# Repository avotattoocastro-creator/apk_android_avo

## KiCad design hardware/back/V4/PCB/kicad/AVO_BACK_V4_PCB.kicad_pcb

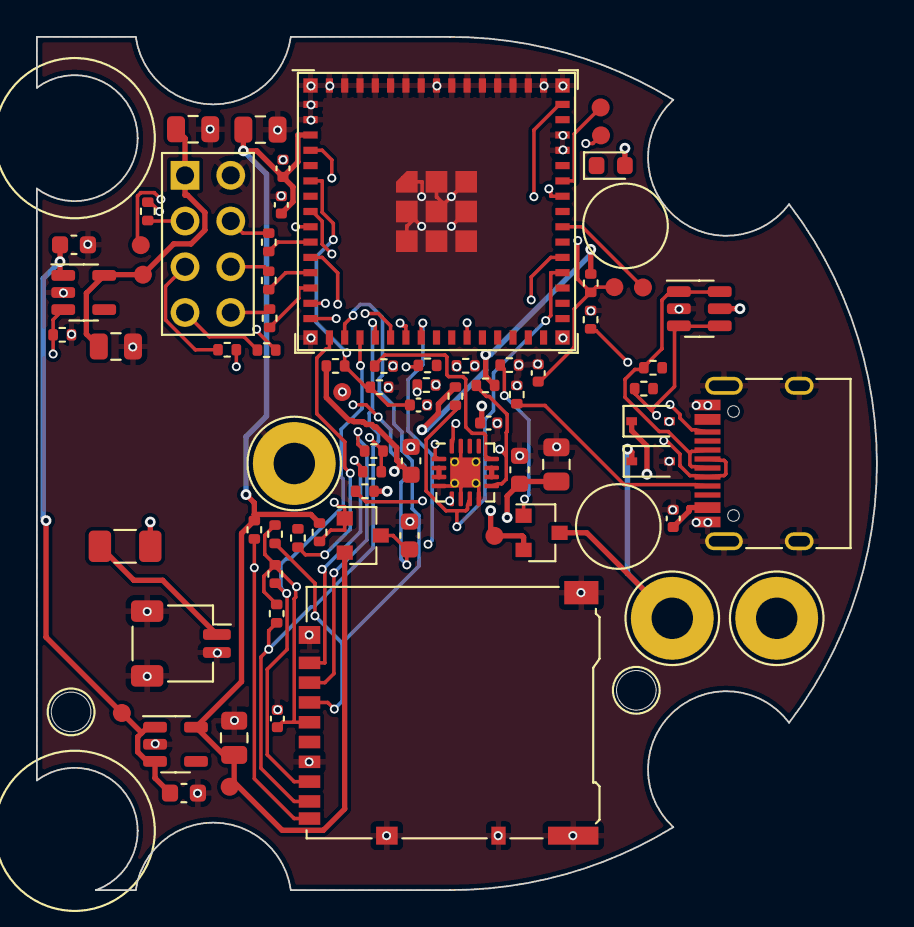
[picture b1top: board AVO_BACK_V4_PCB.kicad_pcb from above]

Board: 4 copper layers, 46.7 x 47.4 mm, 81 parts (0 on the bottom side), 53 nets.

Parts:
C18, C26, C27, C28: 1u; C_0402_1005Metric
C19, C20, C21, C40, C60: 10u 25V; C_0603_1608Metric
C22, C24, C61: 22u 10V; C_0805_2012Metric
C25, C34, C41: 100n; C_0402_1005Metric
C35, C62: 47u 6V3; C_0805_2012Metric
D1: LED rojo; LED_0603_1608Metric
D2, D3: TVS 5 V; D_SOD-323
F1: PTC 1,5 A; Fuse_1206_3216Metric
H1, H2: PIVOTE; AVO_Pivote_NPTH_D2.2
J1: USB-C 16P; USB_C_Receptacle_HRO_TYPE-C-31-M-12
J2: BATERÍA 1S; JST_SH_SM02B-SRSS-TB_1x02-1MP_P1.00mm_Horizontal
J3: microSD DM3AT; microSD_HC_Hirose_DM3AT-SF-PEJM5
J4: URTK1.2 (8 hilos); AVO_URTK_Pads_2x04_P2.54mm
MP1, MP2: PISADOR; AVO_Zona_Libre_R2.5
MR1, MR2: ANILLO; AVO_Zona_Libre_R4.6
P1: CONTACTO SYS; AVO_Contacto_M2_Tornillo
P2: CONTACTO BAT; AVO_Contacto_M2_Tornillo
P3: CONTACTO GND; AVO_Contacto_M2_Tornillo
Q3, Q4: AO3401A; SOT-23
R6, R7: 2k; R_0402_1005Metric
R8, R9, R10, R40, R47, R60: 100k; R_0402_1005Metric
R11, R30, R41, R42, R43, R44, R45: 10k; R_0402_1005Metric
R15, R50, R51, R52: 1k; R_0402_1005Metric
R16, R17: 5k1; R_0402_1005Metric
R18, R19, R46: 22R; R_0402_1005Metric
R32, R33: 1M; R_0402_1005Metric
R53, R54, R55: 330R; R_0402_1005Metric
RT2: NTC 10k B3380; R_0402_1005Metric
TP1: EN; TestPoint_Pad_D1.0mm
TP2: BOOT; TestPoint_Pad_D1.0mm
TP3: GND; TestPoint_Pad_D1.0mm
TP4: TXD0; TestPoint_Pad_D1.0mm
TP5: RXD0; TestPoint_Pad_D1.0mm
TP6: 3V3; TestPoint_Pad_D1.0mm
TP7: VBAT; TestPoint_Pad_D1.0mm
TP8: VSYS; TestPoint_Pad_D1.0mm
TP9: 3V3_ZED; TestPoint_Pad_D1.0mm
TP10: GPIO41; TestPoint_Pad_D1.0mm
U2: BQ24072RGTR; VQFN-16-1EP_3x3mm_P0.5mm_EP1.68x1.68mm_ThermalVias
U3: TLV75733PDBVR; SOT-23-5
U4: ESP32-S3-MINI-1U-N8; ESP32-S3-MINI-1U
U6: USBLC6-2SC6; SOT-23-6
U7: RT9080-33GJ5; SOT-23-5

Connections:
+3V3: C22.1, C24.1, C25.1, C26.1, D1.2, Q4.2, R9.2, R10.2, R11.2, R40.2, R47.2, TP6.1, U3.5, U4.3
+3V3_SD: C40.1, C41.1, J3.4, Q4.3, R41.2, R42.2, R43.2, R44.2, R45.2
+3V3_ZED: C61.1, C62.1, J4.1, TP9.1, U7.5
BAT_ADC: C34.1, R32.2, R33.1, U4.6
BAT_F: D3.1, F1.2, P2.1
BAT_G: Q3.1, R30.1
BAT_IN: F1.1, J2.1
BOOT: TP2.1, U4.4
CC1: J1.A5, R16.1
CC2: J1.B5, R17.1
CHG_EN2: R8.1, U2.5
CHG_ILIM: R7.1, U2.12
CHG_ISET: R6.1, U2.16
CHG_PG: R9.1, U2.7, U4.34
CHG_STAT: R10.1, U2.9, U4.35
CHG_TS: RT2.1, U2.1
EN: C27.1, R11.1, TP1.1, U4.45
GND: C18.2, C19.2, C20.2, C21.2, C22.2, C24.2, C25.2, C26.2, C27.2, C28.2, C34.2, C35.2, C40.2, C41.2, C60.2, C61.2, C62.2, D2.2, D3.2, J1.A1, J1.A12, J1.B1, J1.B12, J1.S1, J2.2, J2.MP, J3.6, J3.10, J3.11, J4.2, P3.1, R6.2, R7.2, R16.2, R17.2, R30.2, R33.2, R60.2, RT2.2, TP3.1, U2.4, U2.6, U2.8, U2.15, U2.17, U3.2, U4.1, U4.2, U4.42, U4.43, U4.46, U4.47, U4.48, U4.49, U4.50, U4.51, U4.52, U4.53, U4.54, U4.55, U4.56, U4.57, U4.58, U4.59, U4.60, U4.61, U4.62, U4.63, U4.64, U4.65, U6.2, U7.2
GPIO41: TP10.1, U4.37
LED: R15.1, U4.15
LED_K: D1.1, R15.2
S3_TX1: R50.1, U4.10
S3_TX2: R51.1, U4.12
S3_ZRST: R52.1, U4.13
SD_CD: J3.9, R47.1, U4.22
SD_CLK: J3.5, R46.2
SD_CLK0: R46.1, U4.16
SD_CMD: J3.3, R41.1, U4.17
SD_D0: J3.7, R42.1, U4.18
SD_D1: J3.8, R43.1, U4.19
SD_D2: J3.1, R44.1, U4.20
SD_D3: J3.2, R45.1, U4.21
SD_PWR_N: Q4.1, R40.1, U4.25
SYS_IN: D2.1, P1.1, Q3.3
U0RX: TP5.1, U4.40
U0TX: TP4.1, U4.39
USB_DM: R19.2, U4.23
USB_DM_C: J1.A7, J1.B7, R19.1, U6.3, U6.4
USB_DP: R18.2, U4.24
USB_DP_C: J1.A6, J1.B6, R18.1, U6.1, U6.6
VBAT: C20.1, Q3.2, R32.1, TP7.1, U2.2, U2.3
VBUS: C18.1, C28.1, J1.A4, J1.A9, J1.B4, J1.B9, U2.13, U6.5
VSYS: C19.1, C21.1, C35.1, C60.1, R8.2, TP8.1, U2.10, U2.11, U3.1, U3.3, U7.1
ZED_EN: R60.1, U4.14, U7.3
ZED_PPS: R55.2, U4.8
ZED_PPS_C: J4.7, R55.1
ZED_RST: J4.8, R52.2
ZED_RX1: J4.4, R50.2
ZED_RX2: J4.6, R51.2
ZED_TX1: R53.2, U4.9
ZED_TX1_C: J4.3, R53.1
ZED_TX2: R54.2, U4.11
ZED_TX2_C: J4.5, R54.1

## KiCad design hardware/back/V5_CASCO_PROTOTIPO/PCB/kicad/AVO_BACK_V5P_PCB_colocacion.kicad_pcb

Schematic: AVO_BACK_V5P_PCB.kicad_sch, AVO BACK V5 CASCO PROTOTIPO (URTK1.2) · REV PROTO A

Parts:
C18, C26, C27, C28, C36, C66, C67: 1u; C_0402_1005Metric; LCSC C52923
C19, C20, C21, C40, C60, C98: 10u 25V; C_0603_1608Metric; LCSC C96446
C22, C24, C35, C61, C99: 22u 10V; C_0805_2012Metric; LCSC C45783
C25, C34, C37, C38, C41, C42, C63, C68, C80, C90, C91, C92, C93, C94, C95, C96, C97: 100n; C_0402_1005Metric; LCSC C1525
C69: 22p; C_0402_1005Metric; LCSC C1555; not fitted
D2, D3: TVS 5 V; D_SOD-323; MPN PESD5V0S1BA; LCSC C2827694
D5, D6: BAT54C; SOT-23; MPN BAT54C; LCSC C2135
D10, D11, D12, D13, D14, D15, D16, D17: SK6812SIDE-A; AVO_SK6812SIDE-A_4.0x1.6mm; MPN SK6812SIDE-A (OPSCO); LCSC C5378721
D18: B5819W; D_SOD-123; MPN B5819W SL; LCSC C8598
F1, F2: PTC 1,5 A; Fuse_1206_3216Metric; MPN SMD1206P150TF; LCSC C20802
J2: BAT +; WirePad_D1.7_Drill0.9
J3: microSD DM3AT; microSD_HC_Hirose_DM3AT-SF-PEJM5; MPN DM3AT-SF-PEJM5; LCSC C114218
J6: BAT −; WirePad_D1.7_Drill0.9
J7: TÁCTIL; WirePad_D1.7_Drill0.9
J10: URTK1.2 9 pines; AVO_URTK1.2_Tira_1x09_P2.54
J11: URTK1.2 10 pines; AVO_URTK1.2_Tira_1x10_P2.54
J12, J13, J14, J15: GND PLACA ANTENA; WirePad_D2.0_Drill1.2
J16: USB-C programación; USB_C_Receptacle_HRO_TYPE-C-31-M-12; MPN TYPE-C-31-M-12 (HRO); LCSC C165948
L71: 1 µH; IND-SMD_L2.0-W1.6_FNR2016XXS; MPN WPN201610U1R0MT (Sunlord); LCSC C97016
P1: POGO VBUS; WirePad_D1.7_Drill0.9
P2: POGO D−; WirePad_D1.7_Drill0.9
P3: POGO D+; WirePad_D1.7_Drill0.9
P4: POGO GND; WirePad_D1.7_Drill0.9
P5: POGO AUX; WirePad_D1.7_Drill0.9
Q4, Q7: AO3401A; SOT-23; LCSC C15127
R6: 1k5; R_0402_1005Metric; LCSC C25867
R7: 2k; R_0402_1005Metric; LCSC C4109
R8, R9, R10, R13, R15, R21, R22, R26, R27, R40, R60: 100k; R_0402_1005Metric; LCSC C25741
R11, R17, R20, R41, R42, R43, R44, R45, R47: 10k; R_0402_1005Metric; LCSC C25744
R12: 68k; R_0402_1005Metric; LCSC C36871
R14, R32, R33: 1M; R_0402_1005Metric; LCSC C26083
R16, R50, R51, R52: 1k; R_0402_1005Metric; LCSC C11702
R18, R19, R46: 22R; R_0402_1005Metric; LCSC C25092
R23: 150k; R_0402_1005Metric; LCSC C25755
R24, R53, R54, R55: 330R; R_0402_1005Metric; LCSC C25104
R25: 620k; R_0402_1005Metric; LCSC C137952
R28, R29: 2k2; R_0402_1005Metric; LCSC C25879
R30, R31: 5k1; R_0402_1005Metric; LCSC C25905
RT2: NTC 10k B3380; R_0402_1005Metric; MPN NCP15XH103F03RC; LCSC C77131
TP1: EN; TestPoint_Pad_D1.0mm
TP2: BOOT; TestPoint_Pad_D1.0mm
TP3: GND; TestPoint_Pad_D1.0mm
TP4: TXD0; TestPoint_Pad_D1.0mm
TP5: RXD0; TestPoint_Pad_D1.0mm
TP6: 3V3; TestPoint_Pad_D1.0mm
TP7: VBAT; TestPoint_Pad_D1.0mm
TP8: VSYS; TestPoint_Pad_D1.0mm
TP9: 3V3_ZED; TestPoint_Pad_D1.0mm
TP10: 3V3_AON; TestPoint_Pad_D1.0mm
TP12: VLED; TestPoint_Pad_D1.0mm
TP13: SAFEBOOT; TestPoint_Pad_D1.0mm
U2: BQ24072RGTR; VQFN-16-1EP_3x3mm_P0.5mm_EP1.68x1.68mm_ThermalVias; MPN BQ24072RGTR; LCSC C140288
U3: TLV75733PDBVR; SOT-23-5; MPN TLV75733PDBVR; LCSC C485517
U4: ESP32-S3-WROOM-1U-N16R8; ESP32-S3-WROOM-1U; MPN ESP32-S3-WROOM-1U-N16R8; LCSC C3013946
U6: USBLC6-2SC6; SOT-23-6; LCSC C7519
U7: RT9080-33GJ5; SOT-23-5; MPN RT9080-33GJ5; LCSC C841192
U8: DRV5032FA; SOT-23; MPN DRV5032FADBZR; LCSC C140921
U9: XC6206P332MR; SOT-23; MPN XC6206P332MR-G (Torex); LCSC C5446
U10: TTP223-BA6-TD; SOT-23-6; MPN TTP223-BA6-TD (TDSEMIC); LCSC C42422127
U11: TPS61023DRLR; SOT-563_L1.6-W1.2-P0.50-LS1.6-BR; MPN TPS61023DRLR (TI); LCSC C919459
U12: MAX17048G+T10; TDFN-8_L2.0-W2.0-P0.50-BL-EP1.2; MPN MAX17048G+T10 (Analog Devices); LCSC C2682616
U13: LSM6DSV16X; ST_LGA-14L_2.5x3mm_P0.5mm; MPN LSM6DSV16XTR (ST); LCSC C5267406

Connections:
+3V3: C22.1, C24.1, C25.1, C26.1, C37.1, C38.1, C42.2, C80.1, Q4.2 (S), R9.2, R10.2, R11.2, R28.2, R29.2, R40.2, TP6.1, U3.5 (OUT), U4.2 (3V3), U8.1 (VCC), U13.5 (VDDIO), U13.8 (VDD), U13.12 (CS)
+3V3_AON: C67.1, C68.1, TP10.1, U9.2 (VOUT), U10.5 (VDD)
+3V3_SD: C40.1, C41.1, J3.4 (VDD), Q4.3 (D), R41.2, R42.2, R43.2, R44.2, R45.2
+3V3_ZED: C61.1, C63.1, J10.3 (3V3), J11.2 (3V3), TP9.1, U7.5 (VOUT)
BAT_ADC: C34.1, R32.2, R33.1, U4.38 (IO2 BAT_ADC)
BAT_F: F1.2, Q7.3 (D)
BAT_G: Q7.1 (G), R13.1
BAT_IN: F1.1, J2.1
BOOT: TP2.1, U4.27 (IO0 BOOT)
CHG_EN2: R8.1, U2.5 (EN2)
CHG_ILIM: R7.1, U2.12 (ILIM)
CHG_ISET: R6.1, U2.16 (ISET)
CHG_PG: R9.1, U2.7 (PGOOD), U4.31 (IO38 CHG_PG)
CHG_STAT: R10.1, U2.9 (CHG), U4.32 (IO39 CHG_STAT)
CHG_TMR: R12.1, U2.14 (TMR)
CHG_TS: RT2.1, U2.1 (TS)
EN: C27.1, R11.1, TP1.1, U4.3 (EN EN)
EN_3V3: C28.1, D5.3 (K), D6.3 (K), R14.1, U3.3 (EN)
GND: C18.2, C19.2, C20.2, C21.2, C22.2, C24.2, C25.2, C26.2, C27.2, C28.2, C34.2, C35.2, C36.2, C37.2, C38.2, C40.2, C41.2, C60.2, C61.2, C63.2, C66.2, C67.2, C68.2, C69.2, C80.2, C90.2, C91.2, C92.2, C93.2, C94.2, C95.2, C96.2, C97.2, C98.2, C99.2, D2.2 (A), D3.2 (A), D10.4 (GND), D11.4 (GND), D12.4 (GND), D13.4 (GND), D14.4 (GND), D15.4 (GND), D16.4 (GND), D17.4 (GND), J3.6 (VSS), J3.10 (DET_COM), J3.11 (SHELL), J6.1, J10.1 (GND), J11.1 (GND), J12.1, J13.1, J14.1, J15.1, J16.A1 (GND), J16.A12 (GND), J16.B1 (GND), J16.B12 (GND), J16.S1 (SHIELD), P4.1, R6.2, R7.2, R12.2, R13.2, R14.2, R15.2, R21.2, R23.2, R26.2, R27.2, R30.2, R31.2, R33.2, R60.2, RT2.2, TP3.1, U2.4 (CE), U2.6 (EN1), U2.8 (VSS), U2.15 (TD), U2.17 (EP), U3.2 (GND), U4.1 (GND), U4.40 (GND), U4.41 (GND), U6.2 (GND), U7.2 (GND), U8.3 (GND), U9.1 (VSS), U10.2 (VSS), U10.4 (AHLB), U10.6 (TOG), U11.4 (GND), U12.1 (CTG), U12.4 (GND), U12.6 (QSTRT), U12.9 (EP), U13.1 (SDO/SA0), U13.2 (SDx), U13.3 (SCx), U13.6 (GND), U13.7 (GND)
HALL: U4.39 (IO1 HALL), U8.2 (OUT)
I2C_SCL: R28.1, U4.34 (IO41 I2C_SCL), U12.7 (SCL), U13.13 (SCL)
I2C_SDA: R29.1, U4.35 (IO42 I2C_SDA), U12.8 (SDA), U13.14 (SDA)
IMU_INT1: U4.4 (IO4 IMU_INT1), U13.4 (INT1)
LED_D1: D10.1 (DIN), R24.2
LED_D2: D10.3 (DOUT), D11.1 (DIN)
LED_D3: D11.3 (DOUT), D12.1 (DIN)
LED_D4: D12.3 (DOUT), D13.1 (DIN)
LED_D5: D13.3 (DOUT), D14.1 (DIN)
LED_D6: D14.3 (DOUT), D15.1 (DIN)
LED_D7: D15.3 (DOUT), D16.1 (DIN)
LED_D8: D16.3 (DOUT), D17.1 (DIN)
LED_DIN_S3: R24.1, U4.24 (IO47 LED_DIN_S3)
LED_PWR: R27.1, U4.25 (IO48 LED_PWR), U11.2 (EN)
POGO_AUX: R20.2, R21.1, U4.33 (IO40 POGO_AUX)
POGO_AUX_C: D3.1 (K), P5.1, R20.1
POGO_VBUS: D2.1 (K), D18.1 (K), F2.1, P1.1
PWR_HOLD: D5.2 (A2), R15.1, U4.16 (IO46 PWR_HOLD)
S3_TX1: R50.1, U4.6 (IO6 S3_TX1)
S3_TX2: R51.1, U4.12 (IO8 S3_TX2)
S3_ZRST: R52.1, U4.17 (IO9 S3_ZRST)
SD_CLK: J3.5 (CLK), R46.2
SD_CLK0: R46.1, U4.20 (IO12 SD_CLK0)
SD_CMD: J3.3 (CMD), R41.1, U4.21 (IO13 SD_CMD)
SD_D0: J3.7 (DAT0), R42.1, U4.22 (IO14 SD_D0)
SD_D1: J3.8 (DAT1), R43.1, U4.8 (IO15 SD_D1)
SD_D2: J3.1 (DAT2), R44.1, U4.9 (IO16 SD_D2)
SD_D3: J3.2 (CD/DAT3), R45.1, U4.10 (IO17 SD_D3)
SD_G: C42.1, Q4.1 (G), R40.1, R47.2
SD_PWR_N: R47.1, U4.23 (IO21 SD_PWR_N)
TOUCH_E: J7.1, R16.1
TOUCH_I: C69.1, R16.2, U10.3 (I)
TOUCH_OUT: D5.1 (A1), R17.1, U10.1 (Q)
TOUCH_SENSE: R17.2, U4.19 (IO11 TOUCH_SENSE)
U0RX: TP5.1, U4.36 (RXD0 U0RX)
U0TX: TP4.1, U4.37 (TXD0 U0TX)
USBC_CC1: J16.A5 (CC1), R30.1
USBC_CC2: J16.B5 (CC2), R31.1
USBC_VBUS: D18.2 (A), J16.A4 (VBUS), J16.A9 (VBUS), J16.B4 (VBUS), J16.B9 (VBUS)
USB_DM: R19.2, U4.13 (IO19 D- USB_DM)
USB_DM_C: J16.A7 (D-), J16.B7 (D-), P2.1, R19.1, U6.3 (IO2), U6.4 (IO2)
USB_DP: R18.2, U4.14 (IO20 D+ USB_DP)
USB_DP_C: J16.A6 (D+), J16.B6 (D+), P3.1, R18.1, U6.1 (IO1), U6.6 (IO1)
VBAT: C20.1, C36.1, C66.1, Q7.2 (S), R32.1, TP7.1, U2.2 (BAT), U2.3 (BAT), U9.3 (VIN), U12.2 (CELL), U12.3 (VDD)
VBUS: C18.1, F2.2, R22.1, U2.13 (IN), U6.5 (VBUS)
VBUS_DET: D6.1 (A1), R22.2, R23.1, U4.11 (IO18 VBUS_DET)
VLED: C90.1, C91.1, C92.1, C93.1, C94.1, C95.1, C96.1, C97.1, C99.1, D10.2 (VDD), D11.2 (VDD), D12.2 (VDD), D13.2 (VDD), D14.2 (VDD), D15.2 (VDD), D16.2 (VDD), D17.2 (VDD), R25.1, TP12.1, U11.6 (VOUT)
VLED_FB: R25.2, R26.1, U11.1 (FB)
VLED_SW: L71.2, U11.5 (SW)
VSYS: C19.1, C21.1, C35.1, C60.1, C98.1, L71.1, R8.2, TP8.1, U2.10 (OUT), U2.11 (OUT), U3.1 (IN), U7.1 (VIN), U11.3 (VIN)
ZED_EN: R60.1, U4.18 (IO10 ZED_EN), U7.3 (EN)
ZED_PPS: R55.2, U4.7 (IO7 ZED_PPS)
ZED_PPS_C: J11.7 (PPS), R55.1
ZED_RST: J11.8 (RST), R52.2
ZED_RX1: J10.7 (RX/MOSI), R50.2
ZED_RX2: J10.5 (RX2), R51.2
ZED_SAFEBOOT: J11.9 (SAFE), TP13.1
ZED_TX1: R53.2, U4.5 (IO5 ZED_TX1)
ZED_TX1_C: J10.8 (TX/MISO), R53.1
ZED_TX2: R54.2, U4.15 (IO3 ZED_TX2)
ZED_TX2_C: J10.4 (TX2), R54.1

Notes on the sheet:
POGO MAGNÉTICO DE 5 CONTACTOS (por hilos): VBUS · D− · D+ · GND · AUX — carga y USB con el PC · ESD
ENCENDIDO Y APAGADO TOTAL: OR de diodos al EN del 3,3 V (táctil · POWER_HOLD GPIO46 · VBUS)
ANILLO DE LUZ: 7 × SK6812SIDE-A (GPIO47) a 4,3 V con elevador TPS61023 (EN = GPIO48, salida desconectada con EN = 0)
microSD (SDMMC 4 bits) · alimentación conmutada
GNSS EN MÓDULO URTK1.2 (ZED-F9P) POR TIRAS DE PINES: 3,3 V propio con EN (RT9080) · UART1 · UART2 · PPS · RESET
BATERÍA (hilos soldados) · PTC · medida por ADC
CARGADOR CON CAMINO DE POTENCIA (BQ24072) · batería 1S ≥ 2000 mAh
3,3 V PRINCIPAL (TLV75733P, 1 A) · EN = OR(táctil, POWER_HOLD, VBUS)
ESP32-S3-WROOM-1U-N16R8 (16 MB + PSRAM 8 MB) · BLE móvil + ESP-NOW cinchas · arranque
SENSOR HALL DRV5032 · encendido al poner la cápsula en la base del casco
3,3 V SIEMPRE ENCENDIDO (XC6206, ≈ 1 µA): táctil (la URTK1.2 lleva su pila de respaldo)
TÁCTIL SELLADO (TTP223, activo alto, directo) · electrodo por hilo · lectura en GPIO11
MEDIDOR DE BATERÍA MAX17048 (0x36, ModelGauge, ≈ 3 µA)
IMU LSM6DSV16X (0x6A) · INT1 → GPIO4 (despierta por movimiento)
BUS I²C (GPIO41 SCL · GPIO42 SDA, 400 kHz)
PUNTOS DE PRUEBA
Generado por fuente/avo_back_v5_pcb.py (mismo origen de datos que la placa). Las conexiones son etiquetas globales: dos pines con la misma etiqueta están unidos.

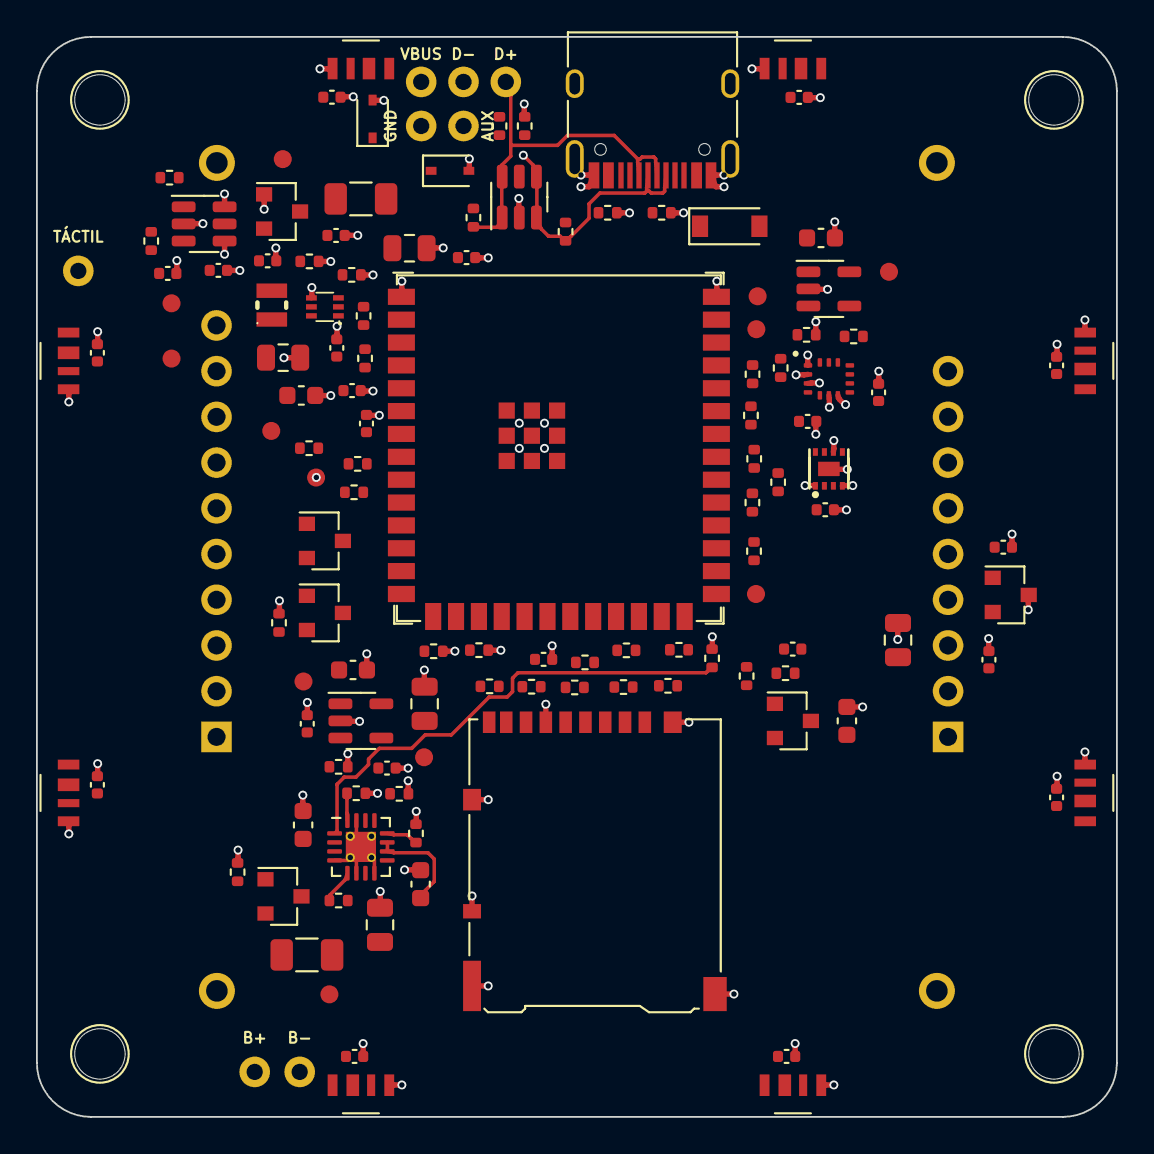
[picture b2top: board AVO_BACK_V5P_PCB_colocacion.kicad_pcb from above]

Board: 4 copper layers, 60.0 x 60.0 mm, 141 parts (0 on the bottom side), 80 nets.

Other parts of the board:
H1, H2, H3, H4: TALADRO M2,5; AVO_Taladro_NPTH_D2.8

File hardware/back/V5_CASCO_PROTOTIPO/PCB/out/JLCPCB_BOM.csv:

Comment,Designator,Footprint,LCSC Part #
"PTC 1,5 A","F1,F2",Fuse_1206_3216Metric,C20802
TVS 5 V,"D2,D3",D_SOD-323,C2827694
10k,"R11,R17,R20,R41,R42,R43,R44,R45,R47",R_0402_1005Metric,C25744
100k,"R8,R9,R10,R13,R15,R21,R27,R40,R60",R_0402_1005Metric,C25741
USBLC6-2SC6,U6,SOT-23-6,C7519
USB-C programación,J16,USB_C_Receptacle_HRO_TYPE-C-31-M-12,C165948
B5819W,D18,D_SOD-123,C8598
5k1,"R30,R31",R_0402_1005Metric,C25905
22R,"R18,R19,R46",R_0402_1005Metric,C25092
1k,"R16,R22,R50,R51,R52",R_0402_1005Metric,C11702
1k5,"R6,R23",R_0402_1005Metric,C25867
BQ24072RGTR,U2,VQFN-16-1EP_3x3mm_P0.5mm_EP1.68x1.68mm_ThermalVias,C140288
1u,"C18,C26,C27,C28,C36,C66,C67",C_0402_1005Metric,C52923
10u 25V,"C19,C20,C21,C40,C60,C98",C_0603_1608Metric,C96446
22u 10V,"C22,C24,C35,C61,C99",C_0805_2012Metric,C45783
2k,"R7,R25",R_0402_1005Metric,C4109
NTC 10k B3380,RT2,R_0402_1005Metric,C77131
68k,R12,R_0402_1005Metric,C36871
AO3401A,"Q4,Q7",SOT-23,C15127
1M,"R14,R32,R33",R_0402_1005Metric,C26083
100n,"C25,C34,C37,C38,C41,C42,C63,C68,C80,C90,C91,C92,C93,C94,C95,C96,C97",C_0402_1005Metric,C1525
TLV75733PDBVR,U3,SOT-23-5,C485517
BAT54C,"D5,D6",SOT-23,C2135
XC6206P332MR,U9,SOT-23,C5446
TTP223-BA6-TD,U10,SOT-23-6,C42422127
RT9080-33GJ5,U7,SOT-23-5,C841192
330R,"R24,R26,R53,R54,R55",R_0402_1005Metric,C25104
ESP32-S3-WROOM-1U-N16R8,U4,ESP32-S3-WROOM-1U,C3013946
SK6812SIDE-A,"D10,D11,D12,D13,D14,D15,D16,D17",AVO_SK6812SIDE-A_4.0x1.6mm,C5378721
TPS61023DRLR,U11,easyeda2kicad:SOT-563_L1.6-W1.2-P0.50-LS1.6-BR,C919459
1 µH,L71,easyeda2kicad:IND-SMD_L2.0-W1.6_FNR2016XXS,C97016
DRV5032FA,U8,SOT-23,C140921
microSD DM3AT,J3,microSD_HC_Hirose_DM3AT-SF-PEJM5,C114218
2k2,"R28,R29",R_0402_1005Metric,C25879
MAX17048G+T10,U12,easyeda2kicad:TDFN-8_L2.0-W2.0-P0.50-BL-EP1.2,C2682616
LSM6DSV16X,U13,ST_LGA-14L_2.5x3mm_P0.5mm,C5267406

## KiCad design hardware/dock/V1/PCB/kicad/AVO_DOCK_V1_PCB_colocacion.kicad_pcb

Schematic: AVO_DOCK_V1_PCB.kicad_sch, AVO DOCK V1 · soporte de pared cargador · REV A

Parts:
C1, C5: 47u 6V3; C_0805_2012Metric; LCSC C16780
C2, C8, C10, C13, C14, C16, C20, C21, C22, C23, C24, C25, C27, C28, C29, C40, C41, C42, C43, C44, C45, C46, C47: 100n; C_0402_1005Metric; LCSC C1525
C3, C15, C48, C49, C50, C51: 10u 25V; C_0603_1608Metric; LCSC C96446
C4: 100u 10V; CP_EIA-3528-21_Kemet-B; MPN TAJB107K010RNJ (AVX) o equivalente
C6, C7, C9: 22u 10V; C_0805_2012Metric; LCSC C45783
C11, C12: 1u; C_0402_1005Metric; LCSC C52923
C26: 4u7; C_0603_1608Metric; LCSC C19666
C30, C31: 18p; C_0402_1005Metric; LCSC C1549
D1, D10, D11, D12, D13, D14, D15, D16, D17: TVS 5 V; D_SOD-323; MPN PESD5V0S1BA; LCSC C2827694
F1: T1A 250V; Fuse_Littelfuse_372_D8.50mm; MPN Littelfuse 37211000411 (TR5, T 1 A)
F2: PTC 1,5 A; Fuse_1206_3216Metric; MPN SMD1206P150TF; LCSC C20802
J1: RED L; WirePad_D2.6_Drill1.3
J2: RED N; WirePad_D2.6_Drill1.3
J3: USB-C PC; USB_C_Receptacle_HRO_TYPE-C-31-M-12; MPN TYPE-C-31-M-12 (HRO); LCSC C165948
J4: PANTALLA 2" ST7789; JST_GH_SM08B-GHS-TB_1x08-1MP_P1.25mm_Horizontal; MPN SM08B-GHS-TB (JST)
P1: A VBUS; WirePad_D1.7_Drill0.9
P2: A D-; WirePad_D1.7_Drill0.9
P3: A D+; WirePad_D1.7_Drill0.9
P4: A GND; WirePad_D1.7_Drill0.9
P5: A AUX; WirePad_D1.7_Drill0.9
P6: B VBUS; WirePad_D1.7_Drill0.9
P7: B D-; WirePad_D1.7_Drill0.9
P8: B D+; WirePad_D1.7_Drill0.9
P9: B GND; WirePad_D1.7_Drill0.9
P10: B AUX; WirePad_D1.7_Drill0.9
P11: GA +5V; WirePad_D1.7_Drill0.9
P12: GA GND; WirePad_D1.7_Drill0.9
P13: GA MTCK; WirePad_D1.7_Drill0.9
P14: GB +5V; WirePad_D1.7_Drill0.9
P15: GB GND; WirePad_D1.7_Drill0.9
P16: GB MTCK; WirePad_D1.7_Drill0.9
P20: PULSADOR; WirePad_D1.7_Drill0.9
P21: PULSADOR GND; WirePad_D1.7_Drill0.9
PS1: IRM-20-5; Converter_ACDC_MeanWell_IRM-20-xx_THT; MPN Mean Well IRM-20-5 (5 V 4 A)
Q1, Q1B, Q2: AO3401A; SOT-23; LCSC C15127
Q3: 2N7002; SOT-23; LCSC C8545
R1, R2, R5, R6, R8, R9, R10, R12, R13, R17, R28, R44, R45, R46, R47: 100k; R_0402_1005Metric; LCSC C25741
R3, R4: 5k1; R_0402_1005Metric; LCSC C25905
R7, R14, R21, R22, R23, R24, R26, R29, R30, R31, R32: 10k; R_0402_1005Metric; LCSC C25744
R11: 0R; R_0402_1005Metric; LCSC C17168
R15, R16, R52, R53, R54, R55: 22R; R_0402_1005Metric; LCSC C25092
R20: 12k; R_0402_1005Metric; LCSC C25752
R27: 68k; R_0402_1005Metric; LCSC C36871
R40, R41: 24k9; R_0402_1005Metric
R42, R43: 49k9; R_0402_1005Metric
R48, R49, R50, R51: 50m 1%; R_0805_2012Metric
R56, R57, R60, R61: 1k; R_0402_1005Metric; LCSC C11702
R62, R63: 47k; R_0402_1005Metric; LCSC C25792
RV1: MOV 275 VAC; RV_Disc_D7mm_W4.8mm_P5mm; MPN S07K275 (TDK) o equivalente
TP1: EN; TestPoint_Pad_D1.0mm
TP2: BOOT; TestPoint_Pad_D1.0mm
TP3: GND; TestPoint_Pad_D1.0mm
TP4: TXD0; TestPoint_Pad_D1.0mm
TP5: RXD0; TestPoint_Pad_D1.0mm
TP6: 3V3; TestPoint_Pad_D1.0mm
TP7: 5V_SYS; TestPoint_Pad_D1.0mm
TP8: 5V_RED; TestPoint_Pad_D1.0mm
TP9: VBUS_PC; TestPoint_Pad_D1.0mm
U1, U18, U19: USBLC6-2SC6; SOT-23-6; LCSC C7519
U2: AMS1117-3.3; SOT-223; MPN AMS1117-3.3; LCSC C6186
U3: ESP32-S3-MINI-1U-N8; ESP32-S3-MINI-1U; MPN ESP32-S3-MINI-1U-N8; LCSC C2980299
U4, U5: TS3USB221; DFN-10-1EP_3x3mm_P0.5mm_EP1.65x2.38mm; MPN TS3USB221ADRCR
U6: USB2514B-I/M2; QFN-36-1EP_6x6mm_P0.5mm_EP3.7x3.7mm_ThermalVias; MPN USB2514B-I/M2 (Microchip); LCSC C220679
U10, U11, U12, U13: TPS2553DBVR; SOT-23-6; MPN TPS2553DBVR (TI)
U14, U15, U16, U17: INA180A2; SOT-23-5; MPN INA180A2IDBVR (TI)
Y1: 24 MHz; Crystal_SMD_3225-4Pin_3.2x2.5mm; MPN X322524MOB4SI (Yangxing) 24 MHz 12 pF o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

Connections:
+3V3: C7.1, C8.1, C9.1, C10.1, C11.1, C13.1, C14.1, C15.1, C20.1, C21.1, C22.1, C23.1, C24.1, C25.1, C26.1, C44.1, C45.1, C46.1, C47.1, J4.2 (VCC), R14.2, R24.2, R26.2, R30.2, R31.2, R32.2, R62.2, R63.2, TP6.1, U2.2 (VOUT), U2.4 (TAB), U3.3 (3V3), U4.10 (VCC), U5.10 (VCC), U6.5 (VDDA33), U6.8 (DN4_DM/PRT_DIS_M4), U6.9 (DN4_DP/PRT_DIS_P4), U6.10 (VDDA33), U6.13 (OCS_N1), U6.15 (VDD33), U6.17 (OCS_N2), U6.19 (OCS_N3), U6.21 (OCS_N4), U6.23 (VDD33), U6.29 (VDDA33), U6.36 (VDDA33), U14.5 (VS), U15.5 (VS), U16.5 (VS), U17.5 (VS)
+5V_RED: C1.1, C2.1, PS1.4 (+V), Q1.3 (D), Q1B.3 (D), R1.1, R7.1, R11.1, TP8.1
+5V_SYS: C4.1 (+), C5.1, C6.1, C40.1, C41.1, C42.1, C43.1, Q1.2 (S), Q1B.2 (S), Q2.2 (S), R8.2, R12.1, TP7.1, U2.3 (VIN), U10.1 (IN), U11.1 (IN), U12.1 (IN), U13.1 (IN)
ACG: Q1.1 (G), Q1B.1 (G), Q3.3 (D), R8.1
ACOK_SNS: R1.2, R2.1, U3.14 (IO10 ACOK_SNS)
AC_L: F1.2, PS1.1 (AC/L), RV1.1
AC_L_IN: F1.1, J1.1
AC_N: J2.1, PS1.2 (AC/N), RV1.2
AUX_A: R56.1, U3.36 (IO40 AUX_A)
AUX_B: R57.1, U3.37 (IO41 AUX_B)
AUX_CA_P: D14.1 (K), P5.1, R56.2
AUX_CB_P: D15.1 (K), P10.1, R57.2
BOOT: TP2.1, U3.4 (IO0 BOOT)
BTN: C16.1, P20.1, R32.1, U3.30 (IO48 BTN)
CA_DM: R53.1, U6.1 (DN1_DM)
CA_DM_P: P2.1, R53.2, U18.3 (IO2), U18.4 (IO2)
CA_DP: R52.1, U6.2 (DN1_DP)
CA_DP_P: P3.1, R52.2, U18.1 (IO1), U18.6 (IO1)
CB_DM: R55.1, U6.3 (DN2_DM)
CB_DM_P: P7.1, R55.2, U19.3 (IO2), U19.4 (IO2)
CB_DP: R54.1, U6.4 (DN2_DP)
CB_DP_P: P8.1, R54.2, U19.1 (IO1), U19.6 (IO1)
CC1: J3.A5 (CC1), R3.1, U3.12 (IO8 CC1)
CC2: J3.B5 (CC2), R4.1, U3.13 (IO9 CC2)
EN: C12.1, R14.1, TP1.1, U3.45 (EN EN)
EN_CA: R44.1, U3.21 (IO17 EN_CA), U10.3 (EN)
EN_CB: R45.1, U3.22 (IO18 EN_CB), U11.3 (EN)
EN_GA: R46.1, U3.25 (IO21 EN_GA), U12.3 (EN)
EN_GB: R47.1, U3.27 (IO47 EN_GB), U13.3 (EN)
FLT_C: R30.1, U3.28 (IO33 FLT_C), U10.4 (FAULT), U11.4 (FAULT)
FLT_G: R31.1, U3.29 (IO34 FLT_G), U12.4 (FAULT), U13.4 (FAULT)
GA_IO_P: D16.1 (K), P13.1, R60.2
GB_IO_P: D17.1 (K), P16.1, R61.2
GIRTH_A_IO: R60.1, R62.1, U3.31 (IO35 GIRTH_A_IO)
GIRTH_B_IO: R61.1, R63.1, U3.32 (IO36 GIRTH_B_IO)
GND: C1.2, C2.2, C3.2, C4.2 (-), C5.2, C6.2, C7.2, C8.2, C9.2, C10.2, C11.2, C12.2, C13.2, C14.2, C15.2, C16.2, C20.2, C21.2, C22.2, C23.2, C24.2, C25.2, C26.2, C27.2, C28.2, C29.2, C30.2, C31.2, C40.2, C41.2, C42.2, C43.2, C44.2, C45.2, C46.2, C47.2, C48.2, C49.2, C50.2, C51.2, D1.2 (A), D10.2 (A), D11.2 (A), D12.2 (A), D13.2 (A), D14.2 (A), D15.2 (A), D16.2 (A), D17.2 (A), J3.A1 (GND), J3.A12 (GND), J3.B1 (GND), J3.B12 (GND), J3.S1 (SHIELD), J4.1 (GND), J4.MP, P4.1, P9.1, P12.1, P15.1, P21.1, PS1.3 (-V), Q3.2 (S), R2.2, R3.2, R4.2, R6.2, R9.2, R10.2, R13.2, R17.2, R20.2, R21.2, R22.2, R23.2, R28.2, R40.2, R41.2, R42.2, R43.2, R44.2, R45.2, R46.2, R47.2, TP3.1, U1.2 (GND), U2.1 (GND), U3.1 (GND), U3.2 (GND), U3.42 (GND), U3.43 (GND), U3.46 (GND), U3.47 (GND), U3.48 (GND), U3.49 (GND), U3.50 (GND), U3.51 (GND), U3.52 (GND), U3.53 (GND), U3.54 (GND), U3.55 (GND), U3.56 (GND), U3.57 (GND), U3.58 (GND), U3.59 (GND), U3.60 (GND), U3.61 (GND), U3.62 (GND), U3.63 (GND), U3.64 (GND), U3.65 (GND), U4.5 (GND), U4.6 (OE), U4.11 (EP), U5.5 (GND), U5.6 (OE), U5.11 (EP), U6.11 (TEST), U6.37 (VSS), U10.2 (GND), U11.2 (GND), U12.2 (GND), U13.2 (GND), U14.2 (GND), U15.2 (GND), U16.2 (GND), U17.2 (GND), U18.2 (GND), U19.2 (GND), Y1.2 (GND), Y1.4 (GND)
HUB_CFG0: R21.1, U6.24 (SCL/CFG_SEL0)
HUB_CFG1: R22.1, U6.25 (HS_IND/CFG_SEL1)
HUB_CRFILT: C27.1, U6.14 (CRFILT)
HUB_DN3_DM: U5.2 (1D-), U6.6 (DN3_DM)
HUB_DN3_DP: U5.1 (1D+), U6.7 (DN3_DP)
HUB_LOCALPWR: R24.1, U6.28 (SUSP_IND/LOCAL_PWR)
HUB_NONREM1: R23.1, U6.22 (SDA/NON_REM1)
HUB_PLLFILT: C28.1, U6.34 (PLLFILT)
HUB_RBIAS: R20.1, U6.35 (RBIAS)
HUB_RST_N: C29.1, R26.1, U3.33 (IO37 HUB_RST_N), U6.26 (RESET_N)
HUB_UP_DM: U4.7 (D-), U6.30 (USBDM_UP)
HUB_UP_DP: U4.8 (D+), U6.31 (USBDP_UP)
HUB_VBUS_DET: R27.2, R28.1, R29.2, U6.27 (VBUS_DET)
HUB_VBUS_EN: R29.1, U3.34 (IO38 HUB_VBUS_EN)
ILIM_CA: R40.1, U10.5 (ILIM)
ILIM_CB: R41.1, U11.5 (ILIM)
ILIM_GA: R42.1, U12.5 (ILIM)
ILIM_GB: R43.1, U13.5 (ILIM)
ISNS_CA: U3.5 (IO1 ISNS_CA), U14.1 (OUT)
ISNS_CB: U3.6 (IO2 ISNS_CB), U15.1 (OUT)
ISNS_GA: U3.8 (IO4 ISNS_GA), U16.1 (OUT)
ISNS_GB: U3.9 (IO5 ISNS_GB), U17.1 (OUT)
LCD_BL: J4.8 (BLK), U3.20 (IO16 LCD_BL)
LCD_CS: J4.7 (CS), U3.17 (IO13 LCD_CS)
LCD_DC: J4.6 (DC), U3.18 (IO14 LCD_DC)
LCD_MOSI: J4.4 (SDA), U3.15 (IO11 LCD_MOSI)
LCD_RST: J4.5 (RES), U3.19 (IO15 LCD_RST)
LCD_SCK: J4.3 (SCL), U3.16 (IO12 LCD_SCK)
RED_DET: Q3.1 (G), R7.2, R10.1
S3H_DM: U4.4 (2D-), U5.4 (2D-)
S3H_DP: U4.3 (2D+), U5.3 (2D+)
S3_DM: R16.1, U3.23 (IO19 D- S3_DM)
S3_DM_R: R16.2, U5.7 (D-)
S3_DP: R15.1, U3.24 (IO20 D+ S3_DP)
S3_DP_R: R15.2, U5.8 (D+)
U0RX: TP5.1, U3.40 (RXD0 U0RX)
U0TX: TP4.1, U3.39 (TXD0 U0TX)
USBC_DM_C: J3.A7 (D-), J3.B7 (D-), U1.3 (IO2), U1.4 (IO2), U4.2 (1D-)
USBC_DP_C: J3.A6 (D+), J3.B6 (D+), U1.1 (IO1), U1.6 (IO1), U4.1 (1D+)
USBG: Q2.1 (G), R9.1, R11.2
USB_SEL: R17.1, U3.35 (IO39 USB_SEL), U4.9 (S), U5.9 (S)
V5_SNS: R12.2, R13.1, U3.10 (IO6 V5_SNS)
VBUSC_SNS: R5.2, R6.1, U3.11 (IO7 VBUSC_SNS)
VBUS_C_RAW: D1.1 (K), F2.1, J3.A4 (VBUS), J3.A9 (VBUS), J3.B4 (VBUS), J3.B9 (VBUS)
VBUS_PC: C3.1, F2.2, Q2.3 (D), R5.1, R27.1, TP9.1, U1.5 (VBUS)
VPOGO_CA: C48.1, D10.1 (K), P1.1, R48.2, U14.4 (IN-), U18.5 (VBUS)
VPOGO_CB: C49.1, D11.1 (K), P6.1, R49.2, U15.4 (IN-), U19.5 (VBUS)
VPOGO_GA: C50.1, D12.1 (K), P11.1, R50.2, U16.4 (IN-)
VPOGO_GB: C51.1, D13.1 (K), P14.1, R51.2, U17.4 (IN-)
VSW_CA: R48.1, U10.6 (OUT), U14.3 (IN+)
VSW_CB: R49.1, U11.6 (OUT), U15.3 (IN+)
VSW_GA: R50.1, U12.6 (OUT), U16.3 (IN+)
VSW_GB: R51.1, U13.6 (OUT), U17.3 (IN+)
XTAL_I: C30.1, U6.33 (XTALIN), Y1.1
XTAL_O: C31.1, U6.32 (XTALOUT), Y1.3

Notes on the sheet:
SELECTOR DE ALIMENTACIÓN: prioridad a la red, sin retroalimentar el PC ni el IRM (PMOS)
USB-C DEL PC: Rd 5,1 k (consumidor) · PTC 1,5 A · ESD
CASCO A: TPS2553 (≈ 1 A) · shunt 50 mΩ + INA180A2 · pogo 5 contactos (VBUS · D− · D+ · GND · AUX)
CASCO B: TPS2553 (≈ 1 A) · shunt 50 mΩ + INA180A2 · pogo 5 contactos
CINCHA A: TPS2553 (≈ 0,5 A) · shunt 50 mΩ + INA180A2 · pogo 3 contactos (+5 V · GND · MTCK)
CINCHA B: TPS2553 (≈ 0,5 A) · shunt 50 mΩ + INA180A2 · pogo 3 contactos
PANTALLA IPS 2,0" ST7789 (JST-GH 8) · pulsador frontal
RED 230 V~ (ZONA AISLADA, FOSO 6,5 mm): fusible T1 A · varistor 275 V · Mean Well IRM-20-5 (5 V 4 A)
3,3 V (AMS1117-3.3)
ESP32-S3-MINI-1U-N8: BLE + Wi-Fi con la app · USB OTG · pantalla · puertos
CONMUTADORES USB TS3USB221: modo PC (USB_SEL = 0) / modo autónomo, S3 anfitrión (USB_SEL = 1)
HUB USB2514B: 1 = casco A · 2 = casco B · 3 = S3 · 4 desactivado · cristal 24 MHz
PUNTOS DE PRUEBA
Generado por fuente/avo_dock_v1_pcb.py (mismo origen de datos que la placa). Las conexiones son etiquetas globales: dos pines con la misma etiqueta están unidos.

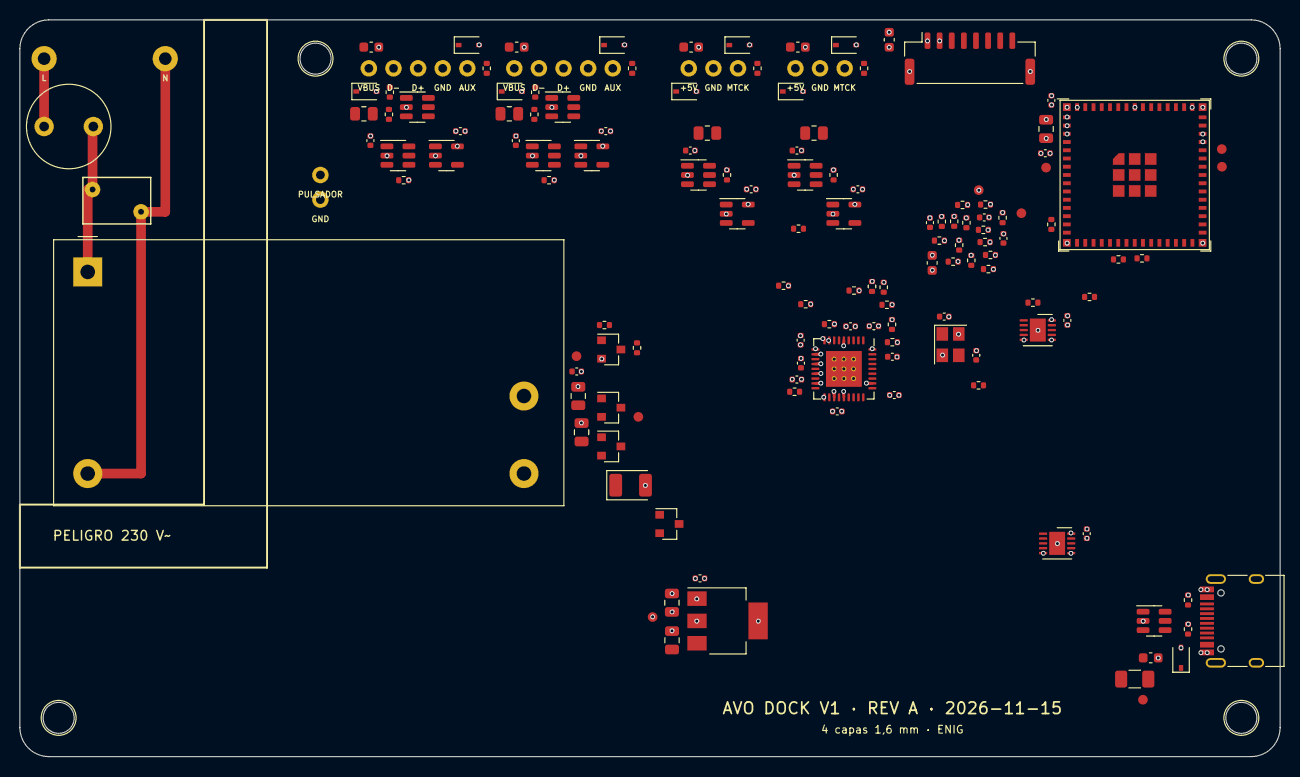
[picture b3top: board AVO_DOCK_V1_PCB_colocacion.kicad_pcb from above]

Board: 4 copper layers, 130.0 x 76.0 mm, 160 parts (0 on the bottom side), 91 nets.

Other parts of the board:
H1, H2, H3, H4: TALADRO M3; AVO_Taladro_NPTH_D3.2

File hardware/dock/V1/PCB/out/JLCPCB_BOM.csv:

Comment,Designator,Footprint,LCSC Part #
47u 6V3,"C1,C5",C_0805_2012Metric,C16780
100n,"C2,C8,C10,C13,C14,C16,C20,C21,C22,C23,C24,C25,C27,C28,C29,C40,C41,C42,C43,C44,C45,C46,C47",C_0402_1005Metric,C1525
100k,"R1,R2,R5,R6,R8,R9,R10,R12,R13,R17,R28,R44,R45,R46,R47",R_0402_1005Metric,C25741
USB-C PC,J3,USB_C_Receptacle_HRO_TYPE-C-31-M-12,C165948
5k1,"R3,R4",R_0402_1005Metric,C25905
"PTC 1,5 A",F2,Fuse_1206_3216Metric,C20802
TVS 5 V,"D1,D10,D11,D12,D13,D14,D15,D16,D17",D_SOD-323,C2827694
USBLC6-2SC6,"U1,U18,U19",SOT-23-6,C7519
10u 25V,"C3,C15,C48,C49,C50,C51",C_0603_1608Metric,C96446
AO3401A,"Q1,Q2,Q1B",SOT-23,C15127
2N7002,Q3,SOT-23,C8545
10k,"R7,R14,R21,R22,R23,R24,R26,R29,R30,R31,R32",R_0402_1005Metric,C25744
0R,R11,R_0402_1005Metric,C17168
AMS1117-3.3,U2,SOT-223,C6186
22u 10V,"C6,C7,C9",C_0805_2012Metric,C45783
ESP32-S3-MINI-1U-N8,U3,ESP32-S3-MINI-1U,C2980299
1u,"C11,C12",C_0402_1005Metric,C52923
22R,"R15,R16,R52,R53,R54,R55",R_0402_1005Metric,C25092
USB2514B-I/M2,U6,QFN-36-1EP_6x6mm_P0.5mm_EP3.7x3.7mm_ThermalVias,C220679
4u7,C26,C_0603_1608Metric,C19666
12k,R20,R_0402_1005Metric,C25752
68k,R27,R_0402_1005Metric,C36871
18p,"C30,C31",C_0402_1005Metric,C1549
1k,"R56,R57,R60,R61",R_0402_1005Metric,C11702
47k,"R62,R63",R_0402_1005Metric,C25792
